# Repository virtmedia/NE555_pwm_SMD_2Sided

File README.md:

# NE555_pwm_SMD_2Sided
Smallest version of NE555 PWM generator. Designed to make at home.

Here is two-side version of [this](https://github.com/virtmedia/NE555_pwm_SMD) project.

## Description
Simple, small and cheap PWM regulator on NE555.
You can use it to drive 12V motor, LED strip, Peltier module, lightbulb etc.
PCB dimensions: 16.18 x 18.42 mm. 
Pulse width regulated by standard potentiometer.
You can use any Mosfet in DPAK (TO-252) case as You like and follow your requirements. I am using 2SK3918 from old pc motherboard.

If you want to make it, just download the pdf files , print it and make thermotransfer.
All SMD resistors and capacitors (except C2 on power input, with is 1206, so you can use higher capacity) are in 0603 cases.
You have to make connection between two layers of copper where the vias are.

Supply Voltage: 4.5 - 16V
Current consumption: about 20mA with no load
Output current: depending of used mosfet, limited by traces width - you can reinforce it with wire for more current.
PWM frequency: about 1KHz for the parts values as in schematic. You can adjust them, just keep the conciderations in NE555 datasheet.

Note that due to the construction, there is no full 0-100% regulation. The output goes to the almost 100%, but the bottom limit is a little bit above 0%. 

## Status
  Tested & works well :)
  Files are prepared for the production. Gerber files are generated. The order was received from the jlcpcb:

## Schematic:

## PCB layout:

## BOM
  
* C1   100n 0603 case
* C2   100n-10u 0805-1206 case
* C3   10n 0603 case 
* D1   LL4148 MINIMELF
* D2   LL4148 MINIMELF                    
* D3   LL4148 MINIMELF              
* IC1  NE555D SO-8
* PR1  10K linear potentiometer
* Q1   Generic MOSFET-N in TO252 (DPAK) case                                 
* R1   1K 0603 case
* R2   47R 0603 case
  
## Future
The project looks finished, i have no plan to change it.

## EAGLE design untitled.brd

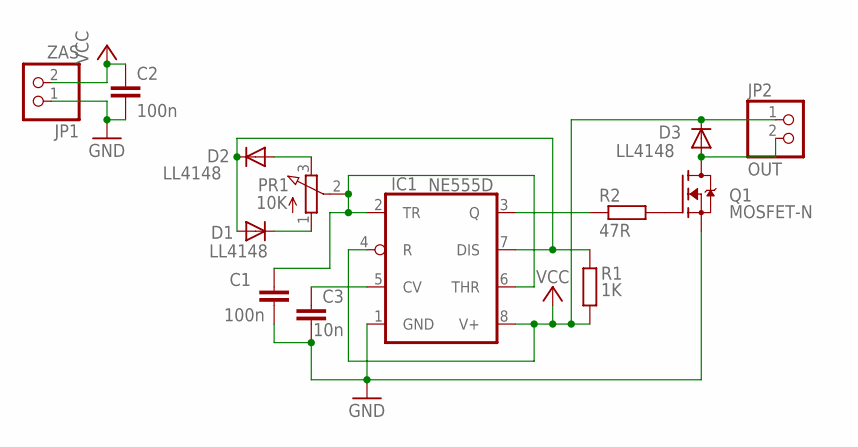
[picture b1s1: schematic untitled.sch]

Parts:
C1: 100n; C0603
C2: 100n; C1206
C3: 10n; C0603
D1, D2, D3: LL4148; MINIMELF
IC1: NE555D; SO08
JP1: ZAS; 1X02
JP2: OUT; 1X02
PR1: 10K; 3RP/1610N
Q1: MOSFET-N; TO252
R1: 1K; R0603
R2: 47R; R0603

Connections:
GND: C1.2, C2.2, C3.2, IC1.1 (GND), JP1.1, Q1.2 (S)
unnamed: C1.1, IC1.2 (TR), IC1.6 (THR), PR1.2 (S)
unnamed: D1.C, PR1.1 (A)
unnamed: D2.A, PR1.3 (E)
unnamed: D1.A, D2.C, IC1.7 (DIS), R1.2
unnamed: IC1.3 (Q), R2.1
unnamed: Q1.1 (G), R2.2
unnamed: C3.1, IC1.5 (CV)
unnamed: D3.A, JP2.2, Q1.3 (D)
VCC: C2.1, D3.C, IC1.4 (R), IC1.8 (V+), JP1.2, JP2.1, R1.1

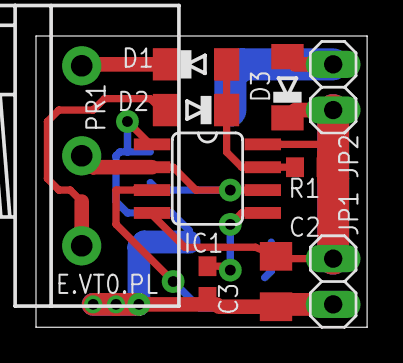
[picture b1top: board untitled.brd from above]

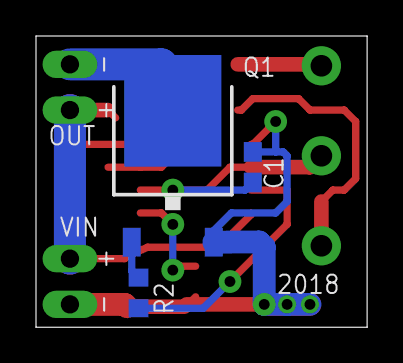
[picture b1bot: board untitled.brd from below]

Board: 2 copper layers, 18.4 x 16.2 mm, 13 parts (3 on the bottom side), 10 nets.

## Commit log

2015-10-07 :neckbeard: Added .gitattributes & .gitignore files
2015-12-02 added image with mount schematic
2018-07-06 Prepared for prodution
2018-07-06 Description update
2018-07-06 Corrected readme file
